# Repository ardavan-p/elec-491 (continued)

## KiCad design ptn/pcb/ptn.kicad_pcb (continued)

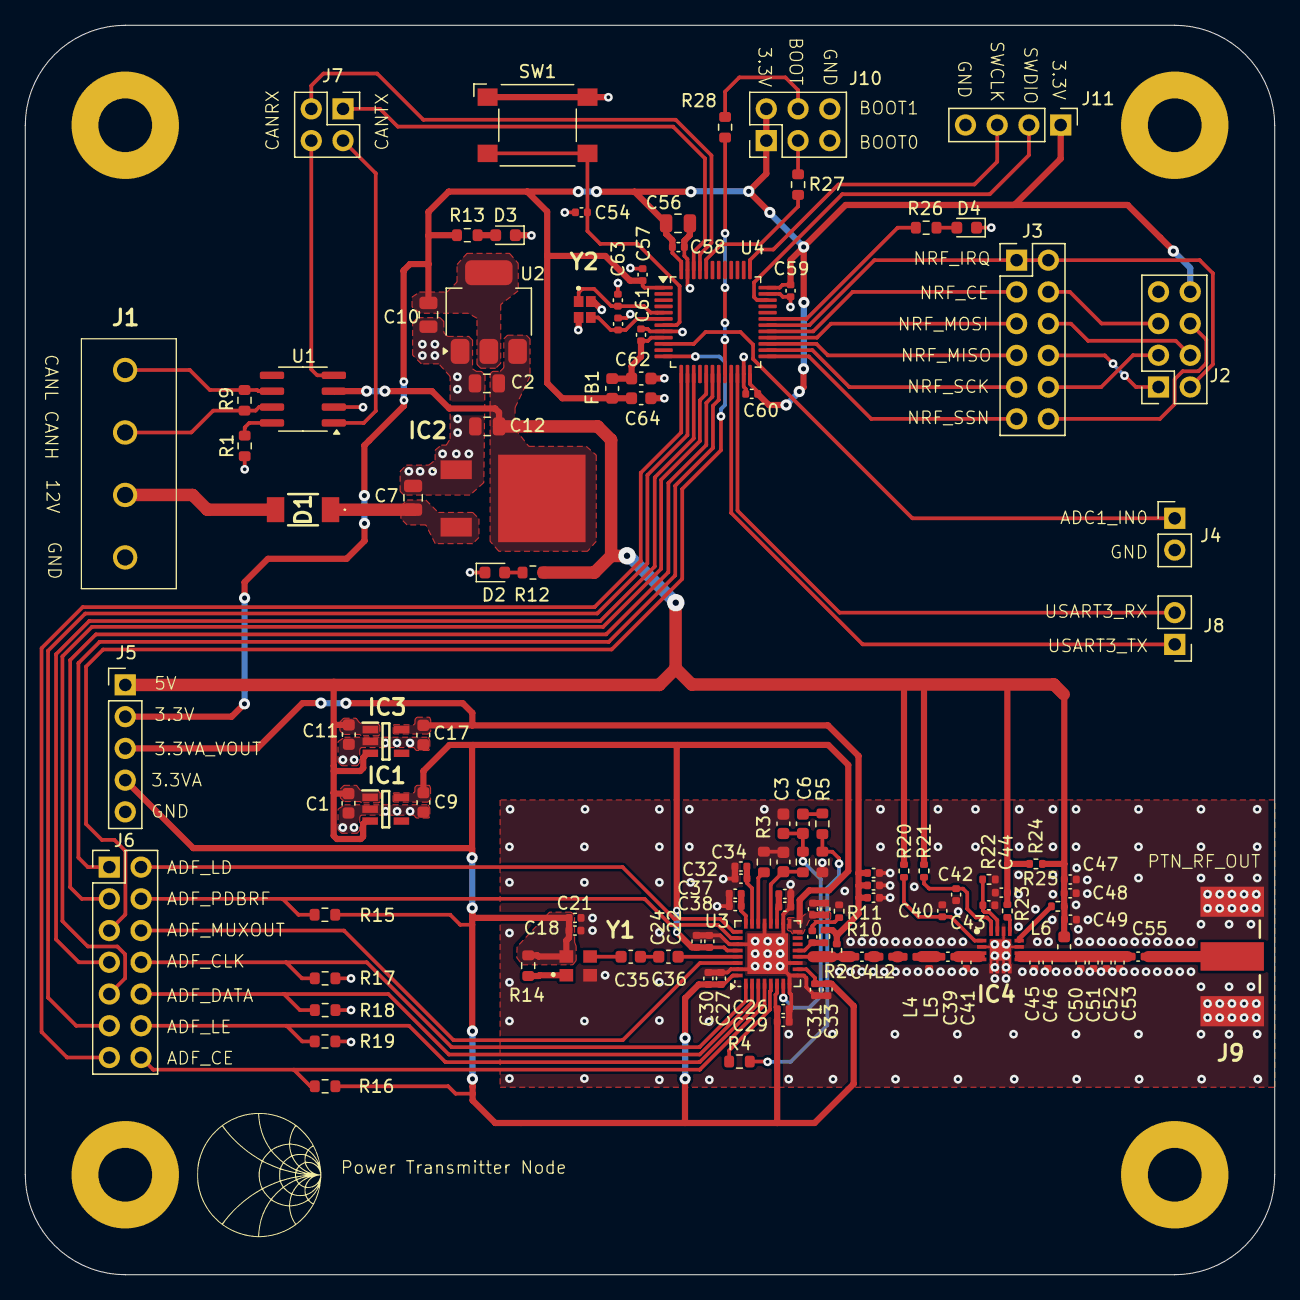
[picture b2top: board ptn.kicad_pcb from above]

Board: 2 copper layers, 100.0 x 100.0 mm, 125 parts (0 on the bottom side), 83 nets.

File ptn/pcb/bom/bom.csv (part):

"Reference","Guerrilla ID","Value","Description","Manufacturer_Name","Manufacturer_Part_Number","Mouser Part Number","Footprint","Qty","Datasheet","DNP"
"J1","","TB002-500-04BE","Fixed Terminal Blocks screw type, 5.00 , horizontal, 4 poles, CUI Blue, slotted screw, PCB mount","CUI Devices","TB002-500-04BE","490-TB002-500-04BE","project_footprint_library:TB00250004BE_SCREW_TERMINAL","1","https://componentsearchengine.com/Datasheets/1/TB002-500-04BE.pdf",""
"SW1","","SW_Push","Push button switch, generic, two pins","Omron Electronics","B3FS-1002P","653-B3FS-1002P","Button_Switch_SMD:SW_SPST_Omron_B3FS-100xP","1","~",""
"U4","","STM32F103C8T6","STMicroelectronics Arm Cortex-M3 MCU, 64KB flash, 20KB RAM, 72 MHz, 2.0-3.6V, 37 GPIO, LQFP48","STMicroelectronics","STM32F103C8T6","511-STM32F103C8T6","Package_QFP:LQFP-48_7x7mm_P0.5mm","1","https://www.st.com/resource/en/datasheet/stm32f103c8.pdf",""
"Y1","","SIT5000AICGE-33E0-25.000000X","TCXO Oscillators 25MHz 3.3V -40C +85C 5ppm","SiTime","SIT5000AICGE-33E0-25.000000X","788-5000AICGE3E0-25X","project_footprint_library:SIT5000AICGE33E025000000X","1","https://componentsearchengine.com/Datasheets/1/SIT5000AICGE-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",""
"U2","","NCP1117-3.3_SOT223","1A Low drop-out regulator, Fixed Output 3.3V, SOT-223","onsemi","NCP1117ST33T3G","863-NCP1117ST33T3G","Package_TO_SOT_SMD:SOT-223-3_TabPin2","1","http://www.onsemi.com/pub_link/Collateral/NCP1117-D.PDF",""
"U1","","MCP2551-I-SN","High-Speed CAN Transceiver, 1Mbps, 5V supply, SOIC-8","Microchip Technology","MCP2551-I/SN","579-MCP2551-I/SN","Package_SO:SOIC-8_3.9x4.9mm_P1.27mm","1","http://ww1.microchip.com/downloads/en/devicedoc/21667d.pdf",""
"D2,D3,D4","","LED","Light emitting diode 150060VS55040","Wurth Elektronik","150060VS55040","710-150060VS55040","LED_SMD:LED_0603_1608Metric","3","~",""
"IC4","","GRF5509","RF Amplifier High Efficiency, 5.0Watt PA/Saturated PA, OP1dB >34.0 dBm, 900 MHz ISM; 0.7 - 01.8 GHz","Guerrilla RF","GRF5509","459-GRF5509","project_footprint_library:QFN50P300X300X85-17N","1","https://www.guerrilla-rf.com/products/DataSheet?sku=5509&fil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",""
"D1","","D","Diode","ROHM Semiconductor","RF302LAM2STR","755-RF302LAM2STR","project_footprint_library:RF302LAM2STR_DIODE","1","~",""
"IC2","","AZ1084CD-5.0TRG1","Linear Voltage Regulator IC Positive Fixed 1 Output 5A TO-252-3","Diodes Incorporated","AZ1084CD-5.0TRG1","621-AZ1084CD-5.0TRG1","project_footprint_library:AZ1084CD50TRG1_LDO_5V","1","https://www.diodes.com//assets/Datasheets/AZ1084C.pdf",""
"IC1,IC3","","ADP150AUJZ-3.3-R7","Ultralow Noise, 150 mA CMOS Linear Regulator","Analog Devices","ADP150AUJZ-3.3-R7","584-ADP150AUJZ-3.3R7","project_footprint_library:SOT95P280X100-5N","2","https://componentsearchengine.com/Datasheets/1/ADP150AUJZ-3.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",""
"U3","","ADF4351","35-4400MHz fractional-N PLL, LFCSP-32","Analog Devices","ADF4351BCPZ-RL7","584-ADF4351BCPZ-R7","Package_CSP:LFCSP-32-1EP_5x5mm_P0.5mm_EP3.25x3.25mm","1","https://www.analog.com/media/en/technical-documentation/data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",""
"J9","","142-0701-801","JOHNSON - 142-0701-801 - \u5C04\u9891/\u540C\u8F74\u63D2\u5B54, SMA, PCB\u5B89\u88C5","Cinch Connectivity Solutions","142-0701-801","530-142-0701-801","project_footprint_library:142-0701-851","1","",""
"Y2","","16MHz","Four pin crystal, GND on pins 2 and 4. Wurth PN: 830108288709","Wurth Elektronik","830108288709","710-830108288709","project_footprint_library:16MHz_830108288709","1","~",""
"R15,R16,R17,R18,R19,R27,R28","","10k","Resistor","YAGEO","RT0603FRE1310KL","603-RT0603FRE1310KL","Resistor_SMD:R_0603_1608Metric","7","~",""
"R21","M3","6.8k","Resistor M3","Panasonic","ERJ-2GEJ682X","667-ERJ-2GEJ682X","Resistor_SMD:R_0402_1005Metric","1","~",""
"R3","","5.1k","Resistor","Vishay / Dale","CRCW06035K10FKEC","71-CRCW06035K10FKEC","Resistor_SMD:R_0603_1608Metric","1","~",""
"R20","M1","3.3k","Resistor M1","Panasonic","ERJ-2GEJ332X","667-ERJ-2GEJ332X","Resistor_SMD:R_0402_1005Metric","1","~",""
"R14","","2k","Resistor","YAGEO","RT0603FRE102KL","603-RT0603FRE102KL","Resistor_SMD:R_0603_1608Metric","1","~",""
"R1,R6","","1k","Resistor","YAGEO","RC0603FR-101KL","603-RC0603FR-101KL","Resistor_SMD:R_0603_1608Metric","2","~",""
"R5","","360R","Resistor","YAGEO","RT0603DRE07360RL","603-RT0603DRE07360RL","Resistor_SMD:R_0603_1608Metric","1","~",""
"R12","","250R","Resistor","YAGEO","RT0603BRE07250RL","603-RT0603BRE07250RL","Resistor_SMD:R_0603_1608Metric","1","~",""
"R9","","120R","Resistor","YAGEO","RC0603FR-10120RL","603-RC0603FR-10120RL","Resistor_SMD:R_0603_1608Metric","1","~",""
"FB1","","120R","Ferrite bead - 120 ohms at 100MHz","Bussmann / Eaton","MFBM1V1608-121-R","704-MFBM1V1608-121-R","Inductor_SMD:L_0603_1608Metric","1","~",""
"R13,R26","","100R","Resistor","YAGEO","RT0603DRE07100RL","603-RT0603DRE07100RL","Resistor_SMD:R_0603_1608Metric","2","~",""
"R2,R10,R11","","50R","Resistor","YAGEO","RC0402JR-0750RL","603-RC0402JR-0750RL","Resistor_SMD:R_0402_1005Metric","3","~",""
"C12","","22u","Unpolarized capacitor","Murata Electronics","GRM21BR61E226ME44K","81-GRM21BR61E226ME4K","Capacitor_SMD:C_0805_2012Metric","1","~",""
"C2,C7,C10,C56","","10u","Unpolarized capacitor","Murata Electronics","GRM21BR61E106KA73K","81-GRM21BR61E106KA3K","Capacitor_SMD:C_0805_2012Metric","4","~",""
"C1,C9,C11,C17,C62,C64","","1u","Unpolarized capacitor","KEMET","C0603C105K3PACTU","80-C0603C105K3P","Capacitor_SMD:C_0603_1608Metric","6","~",""
"C19,C20,C21,C24,C28,C29,C30,C33,C34,C38,C44,C48,C54,C57,C58,C59,C60","-- mixed values --","0.1u","-- mixed values --","Murata Electronics","GRM155R71C104JA88J","81-GRM155R71C104JA8J","Capacitor_SMD:C_0402_1005Metric","17","~",""
"C6","","47n","Unpolarized capacitor","KEMET","C0603C473J3RACTU","80-C0603C473J3R","Capacitor_SMD:C_0603_1608Metric","1","~",""
"L6","M18","24n","Inductor M18","Murata Electronics","LQW18AN24NG80D","81-LQW18AN24NG80D","Inductor_SMD:L_0603_1608Metric","1","~",""
"C61","","10n","Unpolarized capacitor","KEMET","C0402C103J8RACTU","80-C0402C103J8RACTU","Capacitor_SMD:C_0402_1005Metric","1","~",""
"L1,L3","","7.5n","Inductor","Murata Electronics","LQW15AN7N5G80D","81-LQW15AN7N5G80D","Inductor_SMD:L_0402_1005Metric","2","~","DNP"
"L4,L5","-- mixed values --","6.8n","-- mixed values --","Murata Electronics","LQG15WH6N8G02D","81-LQG15WH6N8G02D","Inductor_SMD:L_0402_1005Metric","2","~",""
"C3","","2.7n","Unpolarized capacitor","KYOCERA AVX","06031C272JAT2A","581-06031C272JAT2A","Capacitor_SMD:C_0603_1608Metric","1","~",""
"L2","","1.9n","Inductor","Murata Electronics","LQG15WZ1N9C02D","81-LQG15WZ1N9C02D","Inductor_SMD:L_0402_1005Metric","1","~",""
"C8","","1.2n","Unpolarized capacitor","KEMET","C0603C122J5RACTU","80-C0603C122J5R","Capacitor_SMD:C_0603_1608Metric","1","~",""
"C35,C36","","1n","Unpolarized capacitor","KYOCERA AVX","06035A102JAT2A","581-06035A102J","Capacitor_SMD:C_0603_1608Metric","2","~",""
"C5,C14","","1n","Unpolarized capacitor","Murata Electronics","GRM1555C1H102FA01D","81-GRM1555C1H102FA1D","Capacitor_SMD:C_0402_1005Metric","2","~","DNP"
"C16,C23","","120p","Unpolarized capacitor","Murata Electronics","GRM1555C1H121FA01D","81-GRM1555C1H121FA1D","Capacitor_SMD:C_0402_1005Metric","2","~",""
"C4,C13,C49","-- mixed values --","100p","-- mixed values --","Murata Electronics","GRM1555C1H101FA01D","81-GRM1555C1H101FA1D","Capacitor_SMD:C_0402_1005Metric","3","~",""
"C55","M23","20p","Unpolarized capacitor M23","Murata Electronics","GJM1555C1H200FB01D","81-GJM1555C1H200FB1D","Capacitor_SMD:C_0402_1005Metric","1","~",""
"C53","M22","12p","Unpolarized capacitor M22","Murata Electronics","GJM1555C1H120FB01D","81-GJM1555C1H120FB1D","Capacitor_SMD:C_0402_1005Metric","1","~",""
"C15,C18,C22,C25,C26,C27,C31,C32,C37,C63,C65","","10p","Unpolarized capacitor","Murata Electronics","GCM1555C1H100JA16J","81-GCM1555C1H100JA6J","Capacitor_SMD:C_0402_1005Metric","11","~",""
"C39","M4","5.6p","Unpolarized capacitor M4","Murata Electronics","GJM1555C1H5R6WB01D","81-GJM1555C1H5R6WB1D","Capacitor_SMD:C_0402_1005Metric","1","~",""
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
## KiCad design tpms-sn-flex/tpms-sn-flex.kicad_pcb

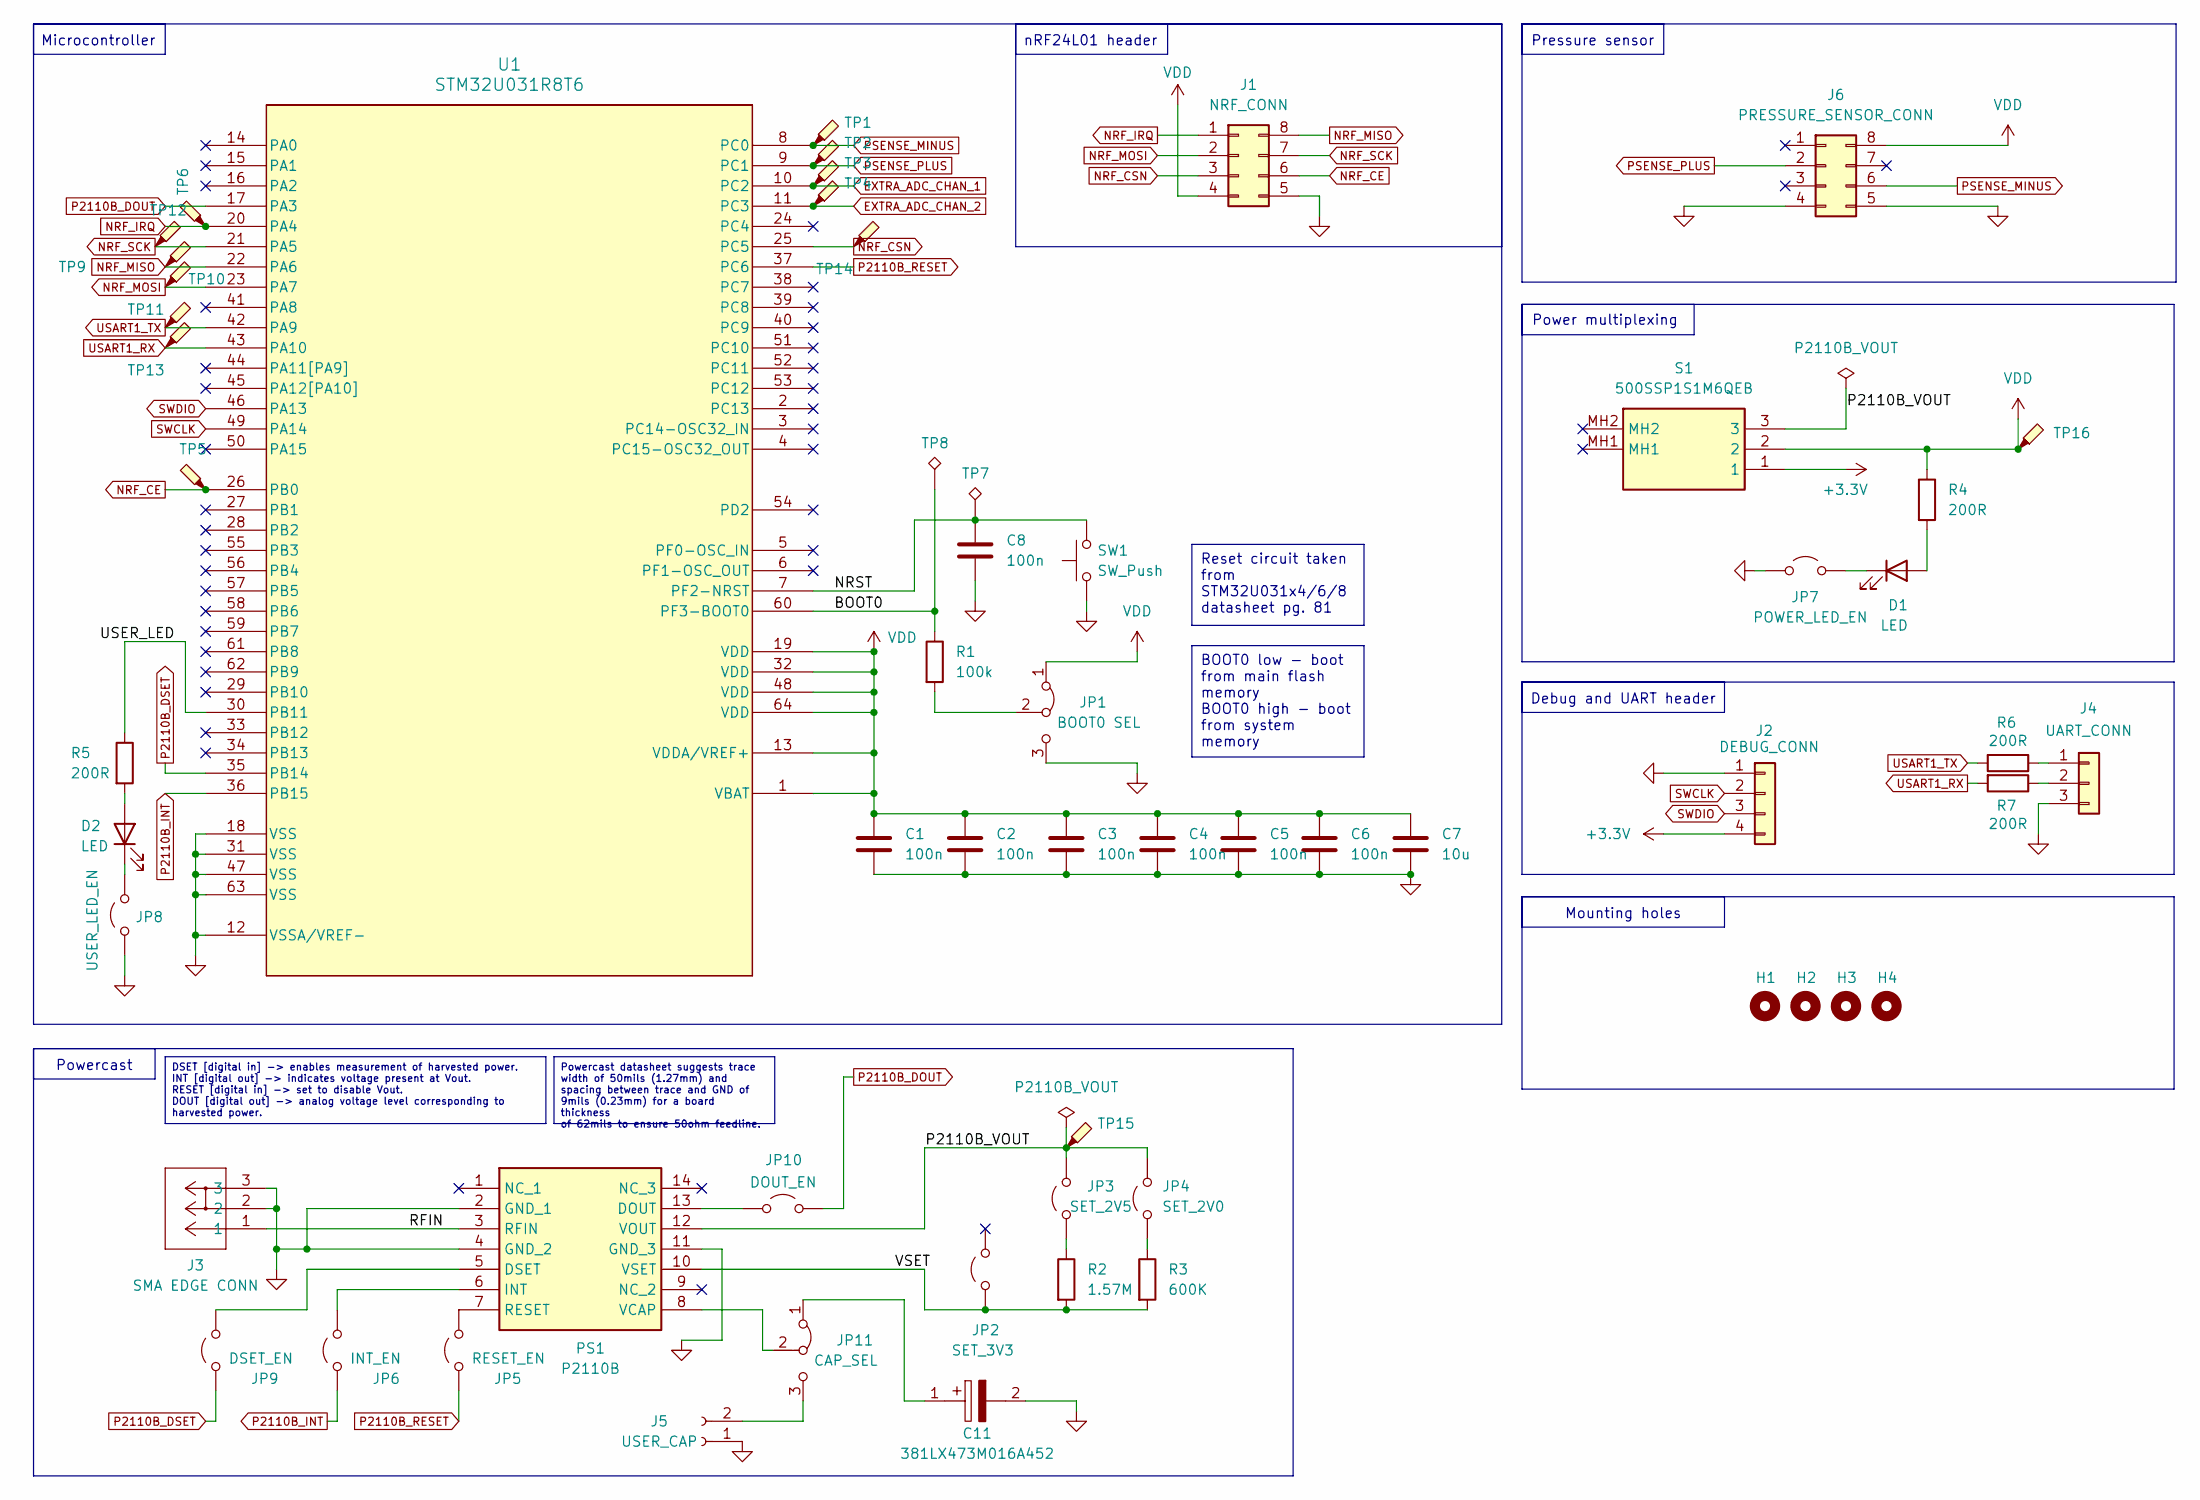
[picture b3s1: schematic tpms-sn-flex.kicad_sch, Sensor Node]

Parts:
C1, C2, C3, C4, C5, C6, C8: 100n; C_0603_1608Metric
C7: 10u; C_0603_1608Metric
C11: 381LX473M016A452; CAPPRD1000W200D3550H4700; Mouser Part Number 598-81LX473M016A452
D1, D2: LED; LED_0603_1608Metric
H1, H2, H3, H4: MountingHole; MountingHole_2.2mm_M2
J1: NRF_CONN; PinSocket_2x04_P2.54mm_Vertical
J2: DEBUG_CONN; PinHeader_1x04_P2.54mm_Vertical
J3: SMA EDGE CONN; CONN_73251-1150_MOL
J4: UART_CONN; PinHeader_1x03_P2.54mm_Vertical
J5: USER_CAP; PinSocket_1x02_P2.54mm_Vertical
J6: PRESSURE_SENSOR_CONN; 8-SOIC-DIP-8-ADAPTER
JP1: BOOT0 SEL; PinHeader_1x03_P2.54mm_Vertical
JP2: SET_3V3; PinHeader_1x02_P2.54mm_Vertical
JP3: SET_2V5; PinHeader_1x02_P2.54mm_Vertical
JP4: SET_2V0; PinHeader_1x02_P2.54mm_Vertical
JP5: RESET_EN; PinHeader_1x02_P2.54mm_Vertical
JP6: INT_EN; PinHeader_1x02_P2.54mm_Vertical
JP7: POWER_LED_EN; PinHeader_1x02_P2.54mm_Vertical
JP8: USER_LED_EN; PinHeader_1x02_P2.54mm_Vertical
JP9: DSET_EN; PinHeader_1x02_P2.54mm_Vertical
JP10: DOUT_EN; PinHeader_1x02_P2.54mm_Vertical
JP11: CAP_SEL; PinHeader_1x03_P2.54mm_Vertical
PS1: P2110B; Mouser Part Number 582-P2110B
R1: 100k; R_0603_1608Metric
R2: 1.57M; R_0603_1608Metric
R3: 600K; R_0603_1608Metric
R4, R5, R6, R7: 200R; R_0603_1608Metric
S1: 500SSP1S1M6QEB; Mouser Part Number 612-500SSP1S1M6QEB
SW1: SW_Push; SW_SPST_Omron_B3FS-100xP
TP1, TP2, TP3, TP4, TP5, TP6: TestPoint_Probe; TestPoint_Pad_2.0x2.0mm
TP7, TP8: TestPoint_Alt; TestPoint_Pad_2.0x2.0mm
TP9, TP10, TP11, TP12, TP13, TP14, TP15, TP16: TestPoint_Pad_2.0x2.0mm
U1: STM32U031R8T6; LQFP64_STM

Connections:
+3.3V: J2.4, S1.1
/BOOT0: R1.1, TP8.1, U1.60 (PF3-BOOT0)
/NRST: C8.1, SW1.2, TP7.1, U1.7 (PF2-NRST)
/P2110B_VOUT: JP3.2 (B), JP4.2 (B), PS1.12 (VOUT), S1.3, TP15.1
/RFIN: J3.1, PS1.3 (RFIN)
/USER_LED: R5.1, U1.30 (PB11)
/VSET: JP2.1 (A), PS1.10 (VSET), R2.2, R3.2
EXTRA_ADC_CHAN_1: TP3.1, U1.10 (PC2)
EXTRA_ADC_CHAN_2: TP4.1, U1.11 (PC3)
GND: C1.2, C2.2, C3.2, C4.2, C5.2, C6.2, C7.2, C8.2, C11.2, H1.1, H2.1, H3.1, H4.1, J1.5, J2.1, J3.2, J3.3, J4.3, J5.1, J6.4, J6.5, JP1.3 (B), JP7.1 (A), JP8.1 (A), PS1.2 (GND_1), PS1.4 (GND_2), PS1.11 (GND_3), SW1.1, U1.12 (VSSA/VREF-), U1.18 (VSS), U1.31 (VSS), U1.47 (VSS), U1.63 (VSS)
NRF_CE: J1.6, TP5.1, U1.26 (PB0)
NRF_CSN: J1.3, TP14.1, U1.25 (PC5)
NRF_IRQ: J1.1, TP6.1, U1.20 (PA4)
NRF_MISO: J1.8, TP9.1, U1.22 (PA6)
NRF_MOSI: J1.2, TP10.1, U1.23 (PA7)
NRF_SCK: J1.7, TP12.1, U1.21 (PA5)
unnamed: D1.2 (A), R4.2
unnamed: D1.1 (K), JP7.2 (B)
unnamed: D2.2 (A), R5.2
unnamed: D2.1 (K), JP8.2 (B)
unnamed: J4.1, R6.1
unnamed: J4.2, R7.1
unnamed: J5.2, JP11.3 (B)
unnamed: JP1.2 (C), R1.2
unnamed: JP3.1 (A), R2.1
unnamed: JP4.1 (A), R3.1
unnamed: JP5.2 (B), PS1.7 (RESET)
unnamed: JP6.2 (B), PS1.6 (INT)
unnamed: JP9.2 (B), PS1.5 (DSET)
unnamed: JP10.1 (A), PS1.13 (DOUT)
unnamed: C11.1, JP11.1 (A)
unnamed: JP11.2 (C), PS1.8 (VCAP)
P2110B_DOUT: JP10.2 (B), U1.17 (PA3)
P2110B_DSET: JP9.1 (A), U1.35 (PB14)
P2110B_INT: JP6.1 (A), U1.36 (PB15)
P2110B_RESET: JP5.1 (A), U1.37 (PC6)
PSENSE_MINUS: J6.6, TP1.1, U1.8 (PC0)
PSENSE_PLUS: J6.2, TP2.1, U1.9 (PC1)
SWCLK: J2.2, U1.49 (PA14)
SWDIO: J2.3, U1.46 (PA13)
USART1_RX: R7.2, TP13.1, U1.43 (PA10)
USART1_TX: R6.2, TP11.1, U1.42 (PA9)
VDD: C1.1, C2.1, C3.1, C4.1, C5.1, C6.1, C7.1, J1.4, J6.8, JP1.1 (A), R4.1, S1.2, TP16.1, U1.1 (VBAT), U1.13 (VDDA/VREF+), U1.19 (VDD), U1.32 (VDD), U1.48 (VDD), U1.64 (VDD)

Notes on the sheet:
Reset circuit taken from STM32U031x4/6/8 datasheet pg. 81
Powercast datasheet suggests trace width of 50mils (1.27mm) and spacing between trace and GND of 9mils (0.23mm) for a board thickness of 62mils to ensure 50ohm feedline.
BOOT0 low - boot from main flash memory BOOT0 high - boot from system memory
DSET [digital in] -> enables measurement of harvested power. INT [digital out] -> indicates voltage present at Vout. RESET [digital in] -> set to disable Vout. DOUT [digital out] -> analog voltage level corresponding to harvested power.
nRF24L01 header
Microcontroller
Powercast
Debug and UART header
Mounting holes
Pressure sensor
Power multiplexing

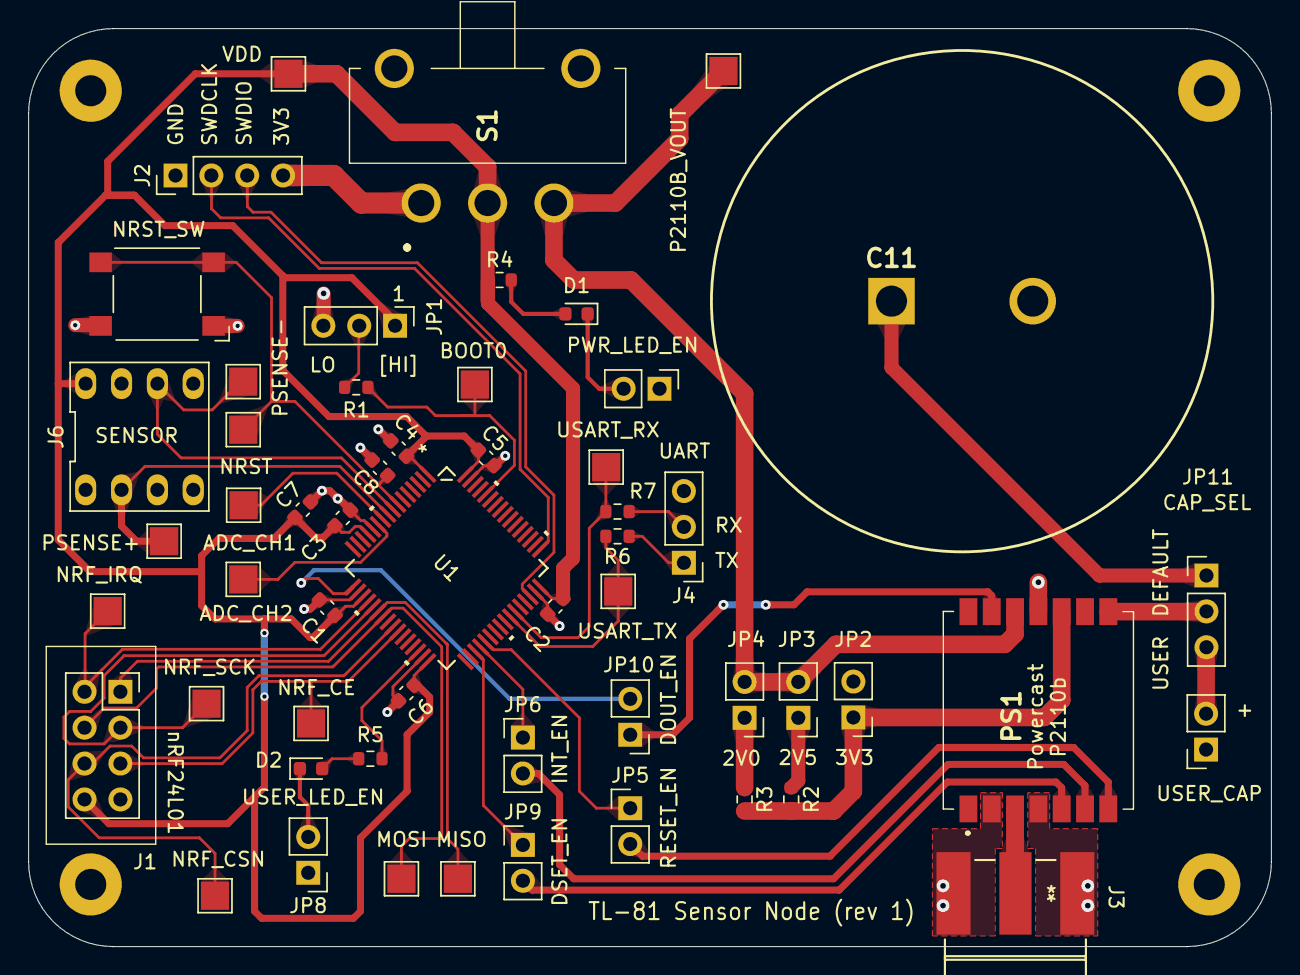
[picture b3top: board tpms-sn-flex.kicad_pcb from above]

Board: 2 copper layers, 88.0 x 65.0 mm, 59 parts (0 on the bottom side), 43 nets.

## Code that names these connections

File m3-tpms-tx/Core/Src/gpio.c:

/* USER CODE BEGIN Header */
/**
  ******************************************************************************
  * @file    gpio.c
  * @brief   This file provides code for the configuration
  *          of all used GPIO pins.
  ******************************************************************************
  * @attention
  *
  * Copyright (c) 2024 STMicroelectronics.
  * All rights reserved.
  *
  * This software is licensed under terms that can be found in the LICENSE file
  * in the root directory of this software component.
  * If no LICENSE file comes with this software, it is provided AS-IS.
  *
  ******************************************************************************
  */
/* USER CODE END Header */

/* Includes ------------------------------------------------------------------*/
#include "gpio.h"

/* USER CODE BEGIN 0 */

/* USER CODE END 0 */

/*----------------------------------------------------------------------------*/
/* Configure GPIO                                                             */
/*----------------------------------------------------------------------------*/
/* USER CODE BEGIN 1 */

/* USER CODE END 1 */

/** Configure pins
     PC14-OSC32_IN   ------> RCC_OSC32_IN
     PC15-OSC32_OUT   ------> RCC_OSC32_OUT
     PF0-OSC_IN   ------> RCC_OSC_IN
     PF1-OSC_OUT   ------> RCC_OSC_OUT
     PA13 (SWDIO)   ------> DEBUG_JTMS-SWDIO
     PA14 (SWCLK)   ------> DEBUG_JTCK-SWCLK
*/
void MX_GPIO_Init(void)
{

  GPIO_InitTypeDef GPIO_InitStruct = {0};

  /* GPIO Ports Clock Enable */
  __HAL_RCC_GPIOC_CLK_ENABLE();
  __HAL_RCC_GPIOF_CLK_ENABLE();
  __HAL_RCC_GPIOA_CLK_ENABLE();
  __HAL_RCC_GPIOB_CLK_ENABLE();
  __HAL_RCC_GPIOD_CLK_ENABLE();

  /*Configure GPIO pin Output Level */
  HAL_GPIO_WritePin(USER_LED_GPIO_Port, USER_LED_Pin, GPIO_PIN_RESET);

  /*Configure GPIO pin Output Level */
  HAL_GPIO_WritePin(GPIOC, P2110B_RESET_Pin|CHIP_SELECT_Pin|CHIP_ENABLE_Pin, GPIO_PIN_RESET);

  /*Configure GPIO pins : PC13 PC0 PC1 PC2
                           PC4 PC5 PC6 PC7
                           PC8 */
  GPIO_InitStruct.Pin = GPIO_PIN_13|GPIO_PIN_0|GPIO_PIN_1|GPIO_PIN_2
                          |GPIO_PIN_4|GPIO_PIN_5|GPIO_PIN_6|GPIO_PIN_7
                          |GPIO_PIN_8;
  GPIO_InitStruct.Mode = GPIO_MODE_ANALOG;
  GPIO_InitStruct.Pull = GPIO_NOPULL;
  HAL_GPIO_Init(GPIOC, &GPIO_InitStruct);

  /*Configure GPIO pins : PF2 PF3 */
  GPIO_InitStruct.Pin = GPIO_PIN_2|GPIO_PIN_3;
  GPIO_InitStruct.Mode = GPIO_MODE_ANALOG;
  GPIO_InitStruct.Pull = GPIO_NOPULL;
  HAL_GPIO_Init(GPIOF, &GPIO_InitStruct);

  /*Configure GPIO pins : PA0 PA2 PA3 PA4
                           PA8 PA9 PA10 PA11
                           PA12 PA15 */
  GPIO_InitStruct.Pin = GPIO_PIN_0|GPIO_PIN_2|GPIO_PIN_3|GPIO_PIN_4
                          |GPIO_PIN_8|GPIO_PIN_9|GPIO_PIN_10|GPIO_PIN_11
                          |GPIO_PIN_12|GPIO_PIN_15;
  GPIO_InitStruct.Mode = GPIO_MODE_ANALOG;
  GPIO_InitStruct.Pull = GPIO_NOPULL;
  HAL_GPIO_Init(GPIOA, &GPIO_InitStruct);

  /*Configure GPIO pin : PtPin */
  GPIO_InitStruct.Pin = USER_LED_Pin;
  GPIO_InitStruct.Mode = GPIO_MODE_OUTPUT_PP;
  GPIO_InitStruct.Pull = GPIO_NOPULL;
  GPIO_InitStruct.Speed = GPIO_SPEED_FREQ_LOW;
  HAL_GPIO_Init(USER_LED_GPIO_Port, &GPIO_InitStruct);

  /*Configure GPIO pins : PB0 PB1 PB2 PB10
                           PB11 PB12 PB13 PB14
                           PB15 PB3 PB4 PB5
                           PB6 PB7 PB8 PB9 */
  GPIO_InitStruct.Pin = GPIO_PIN_0|GPIO_PIN_1|GPIO_PIN_2|GPIO_PIN_10
                          |GPIO_PIN_11|GPIO_PIN_12|GPIO_PIN_13|GPIO_PIN_14
                          |GPIO_PIN_15|GPIO_PIN_3|GPIO_PIN_4|GPIO_PIN_5
                          |GPIO_PIN_6|GPIO_PIN_7|GPIO_PIN_8|GPIO_PIN_9;
  GPIO_InitStruct.Mode = GPIO_MODE_ANALOG;
  GPIO_InitStruct.Pull = GPIO_NOPULL;
  HAL_GPIO_Init(GPIOB, &GPIO_InitStruct);

  /*Configure GPIO pins : PCPin PCPin PCPin */
  GPIO_InitStruct.Pin = P2110B_RESET_Pin|CHIP_SELECT_Pin|CHIP_ENABLE_Pin;
  GPIO_InitStruct.Mode = GPIO_MODE_OUTPUT_PP;
  GPIO_InitStruct.Pull = GPIO_NOPULL;
  GPIO_InitStruct.Speed = GPIO_SPEED_FREQ_LOW;
  HAL_GPIO_Init(GPIOC, &GPIO_InitStruct);

  /*Configure GPIO pin : PtPin */
  GPIO_InitStruct.Pin = N_IRQ_Pin;
  GPIO_InitStruct.Mode = GPIO_MODE_IT_FALLING;
  GPIO_InitStruct.Pull = GPIO_NOPULL;
  HAL_GPIO_Init(N_IRQ_GPIO_Port, &GPIO_InitStruct);

  /*Configure GPIO pin : PD2 */
  GPIO_InitStruct.Pin = GPIO_PIN_2;
  GPIO_InitStruct.Mode = GPIO_MODE_ANALOG;
  GPIO_InitStruct.Pull = GPIO_NOPULL;
  HAL_GPIO_Init(GPIOD, &GPIO_InitStruct);

  /* EXTI interrupt init*/
  HAL_NVIC_SetPriority(EXTI4_15_IRQn, 0, 0);
  HAL_NVIC_EnableIRQ(EXTI4_15_IRQn);

}

/* USER CODE BEGIN 2 */

/* USER CODE END 2 */

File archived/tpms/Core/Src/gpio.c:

/* USER CODE BEGIN Header */
/**
  ******************************************************************************
  * @file    gpio.c
  * @brief   This file provides code for the configuration
  *          of all used GPIO pins.
  ******************************************************************************
  * @attention
  *
  * Copyright (c) 2024 STMicroelectronics.
  * All rights reserved.
  *
  * This software is licensed under terms that can be found in the LICENSE file
  * in the root directory of this software component.
  * If no LICENSE file comes with this software, it is provided AS-IS.
  *
  ******************************************************************************
  */
/* USER CODE END Header */

/* Includes ------------------------------------------------------------------*/
#include "gpio.h"

/* USER CODE BEGIN 0 */

/* USER CODE END 0 */

/*----------------------------------------------------------------------------*/
/* Configure GPIO                                                             */
/*----------------------------------------------------------------------------*/
/* USER CODE BEGIN 1 */

/* USER CODE END 1 */

/** Configure pins
     PC14-OSC32_IN   ------> RCC_OSC32_IN
     PC15-OSC32_OUT   ------> RCC_OSC32_OUT
     PF0-OSC_IN   ------> RCC_OSC_IN
     PF1-OSC_OUT   ------> RCC_OSC_OUT
     PA13 (SWDIO)   ------> DEBUG_JTMS-SWDIO
     PA14 (SWCLK)   ------> DEBUG_JTCK-SWCLK
     PB8   ------> I2C1_SCL
     PB9   ------> I2C1_SDA
*/
void MX_GPIO_Init(void)
{

  GPIO_InitTypeDef GPIO_InitStruct = {0};

  /* GPIO Ports Clock Enable */
  __HAL_RCC_GPIOC_CLK_ENABLE();
  __HAL_RCC_GPIOF_CLK_ENABLE();
  __HAL_RCC_GPIOA_CLK_ENABLE();
  __HAL_RCC_GPIOB_CLK_ENABLE();
  __HAL_RCC_GPIOD_CLK_ENABLE();

  /*Configure GPIO pin Output Level */
  HAL_GPIO_WritePin(USER_LED_GPIO_Port, USER_LED_Pin, GPIO_PIN_RESET);

  /*Configure GPIO pin Output Level */
  HAL_GPIO_WritePin(GPIOC, CHIP_SELECT_Pin|CHIP_ENABLE_Pin, GPIO_PIN_RESET);

  /*Configure GPIO pins : PC13 PC0 PC1 PC2
                           PC3 PC4 PC5 PC6
                           PC7 PC8 PC9 */
  GPIO_InitStruct.Pin = GPIO_PIN_13|GPIO_PIN_0|GPIO_PIN_1|GPIO_PIN_2
                          |GPIO_PIN_3|GPIO_PIN_4|GPIO_PIN_5|GPIO_PIN_6
                          |GPIO_PIN_7|GPIO_PIN_8|GPIO_PIN_9;
  GPIO_InitStruct.Mode = GPIO_MODE_ANALOG;
  GPIO_InitStruct.Pull = GPIO_NOPULL;
  HAL_GPIO_Init(GPIOC, &GPIO_InitStruct);

  /*Configure GPIO pins : PF2 PF3 */
  GPIO_InitStruct.Pin = GPIO_PIN_2|GPIO_PIN_3;
  GPIO_InitStruct.Mode = GPIO_MODE_ANALOG;
  GPIO_InitStruct.Pull = GPIO_NOPULL;
  HAL_GPIO_Init(GPIOF, &GPIO_InitStruct);

  /*Configure GPIO pins : PA0 PA4 PA8 PA9
                           PA10 PA11 PA12 PA15 */
  GPIO_InitStruct.Pin = GPIO_PIN_0|GPIO_PIN_4|GPIO_PIN_8|GPIO_PIN_9
                          |GPIO_PIN_10|GPIO_PIN_11|GPIO_PIN_12|GPIO_PIN_15;
  GPIO_InitStruct.Mode = GPIO_MODE_ANALOG;
  GPIO_InitStruct.Pull = GPIO_NOPULL;
  HAL_GPIO_Init(GPIOA, &GPIO_InitStruct);

  /*Configure GPIO pin : PtPin */
  GPIO_InitStruct.Pin = USER_LED_Pin;
  GPIO_InitStruct.Mode = GPIO_MODE_OUTPUT_PP;
  GPIO_InitStruct.Pull = GPIO_NOPULL;
  GPIO_InitStruct.Speed = GPIO_SPEED_FREQ_LOW;
  HAL_GPIO_Init(USER_LED_GPIO_Port, &GPIO_InitStruct);

  /*Configure GPIO pins : PB0 PB1 PB2 PB10
                           PB11 PB12 PB13 PB14
                           PB15 PB3 PB4 PB5
                           PB6 PB7 */
  GPIO_InitStruct.Pin = GPIO_PIN_0|GPIO_PIN_1|GPIO_PIN_2|GPIO_PIN_10
                          |GPIO_PIN_11|GPIO_PIN_12|GPIO_PIN_13|GPIO_PIN_14
                          |GPIO_PIN_15|GPIO_PIN_3|GPIO_PIN_4|GPIO_PIN_5
                          |GPIO_PIN_6|GPIO_PIN_7;
  GPIO_InitStruct.Mode = GPIO_MODE_ANALOG;
  GPIO_InitStruct.Pull = GPIO_NOPULL;
  HAL_GPIO_Init(GPIOB, &GPIO_InitStruct);

  /*Configure GPIO pins : PCPin PCPin */
  GPIO_InitStruct.Pin = CHIP_SELECT_Pin|CHIP_ENABLE_Pin;
  GPIO_InitStruct.Mode = GPIO_MODE_OUTPUT_PP;
  GPIO_InitStruct.Pull = GPIO_NOPULL;
  GPIO_InitStruct.Speed = GPIO_SPEED_FREQ_LOW;
  HAL_GPIO_Init(GPIOC, &GPIO_InitStruct);

  /*Configure GPIO pin : PtPin */
  GPIO_InitStruct.Pin = NRF_IRQ_Pin;
  GPIO_InitStruct.Mode = GPIO_MODE_IT_FALLING;
  GPIO_InitStruct.Pull = GPIO_NOPULL;
  HAL_GPIO_Init(NRF_IRQ_GPIO_Port, &GPIO_InitStruct);

  /*Configure GPIO pin : PD2 */
  GPIO_InitStruct.Pin = GPIO_PIN_2;
  GPIO_InitStruct.Mode = GPIO_MODE_ANALOG;
  GPIO_InitStruct.Pull = GPIO_NOPULL;
  HAL_GPIO_Init(GPIOD, &GPIO_InitStruct);

  /*Configure GPIO pins : PBPin PBPin */
  GPIO_InitStruct.Pin = I2C1_SCL_Pin|I2C1_SDA_Pin;
  GPIO_InitStruct.Mode = GPIO_MODE_AF_OD;
  GPIO_InitStruct.Pull = GPIO_NOPULL;
  GPIO_InitStruct.Speed = GPIO_SPEED_FREQ_LOW;
  GPIO_InitStruct.Alternate = GPIO_AF4_I2C1;
  HAL_GPIO_Init(GPIOB, &GPIO_InitStruct);

  /* EXTI interrupt init*/
  HAL_NVIC_SetPriority(EXTI4_15_IRQn, 0, 0);
  HAL_NVIC_EnableIRQ(EXTI4_15_IRQn);

}

/* USER CODE BEGIN 2 */

/* USER CODE END 2 */

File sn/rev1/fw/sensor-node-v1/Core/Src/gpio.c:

/* USER CODE BEGIN Header */
/**
  ******************************************************************************
  * @file    gpio.c
  * @brief   This file provides code for the configuration
  *          of all used GPIO pins.
  ******************************************************************************
  * @attention
  *
  * Copyright (c) 2024 STMicroelectronics.
  * All rights reserved.
  *
  * This software is licensed under terms that can be found in the LICENSE file
  * in the root directory of this software component.
  * If no LICENSE file comes with this software, it is provided AS-IS.
  *
  ******************************************************************************
  */
/* USER CODE END Header */

/* Includes ------------------------------------------------------------------*/
#include "gpio.h"

/* USER CODE BEGIN 0 */

/* USER CODE END 0 */

/*----------------------------------------------------------------------------*/
/* Configure GPIO                                                             */
/*----------------------------------------------------------------------------*/
/* USER CODE BEGIN 1 */

/* USER CODE END 1 */

/** Configure pins
     PA13 (SWDIO)   ------> DEBUG_JTMS-SWDIO
     PA14 (SWCLK)   ------> DEBUG_JTCK-SWCLK
*/
void MX_GPIO_Init(void)
{

  GPIO_InitTypeDef GPIO_InitStruct = {0};

  /* GPIO Ports Clock Enable */
  __HAL_RCC_GPIOC_CLK_ENABLE();
  __HAL_RCC_GPIOF_CLK_ENABLE();
  __HAL_RCC_GPIOA_CLK_ENABLE();
  __HAL_RCC_GPIOB_CLK_ENABLE();
  __HAL_RCC_GPIOD_CLK_ENABLE();

  /*Configure GPIO pin Output Level */
  HAL_GPIO_WritePin(GPIOC, NRF_CSN_Pin|P2110B_RESET_Pin, GPIO_PIN_RESET);

  /*Configure GPIO pin Output Level */
  HAL_GPIO_WritePin(GPIOB, NRF_CE_Pin|USER_LED_Pin, GPIO_PIN_RESET);

  /*Configure GPIO pins : PC13 PC14 PC15 PC2
                           PC3 PC4 PC7 PC8
                           PC9 PC10 PC11 PC12 */
  GPIO_InitStruct.Pin = GPIO_PIN_13|GPIO_PIN_14|GPIO_PIN_15|GPIO_PIN_2
                          |GPIO_PIN_3|GPIO_PIN_4|GPIO_PIN_7|GPIO_PIN_8
                          |GPIO_PIN_9|GPIO_PIN_10|GPIO_PIN_11|GPIO_PIN_12;
  GPIO_InitStruct.Mode = GPIO_MODE_ANALOG;
  GPIO_InitStruct.Pull = GPIO_NOPULL;
  HAL_GPIO_Init(GPIOC, &GPIO_InitStruct);

  /*Configure GPIO pins : PF0 PF1 PF2 PF3 */
  GPIO_InitStruct.Pin = GPIO_PIN_0|GPIO_PIN_1|GPIO_PIN_2|GPIO_PIN_3;
  GPIO_InitStruct.Mode = GPIO_MODE_ANALOG;
  GPIO_InitStruct.Pull = GPIO_NOPULL;
  HAL_GPIO_Init(GPIOF, &GPIO_InitStruct);

  /*Configure GPIO pins : PA0 PA1 PA2 PA3
                           PA8 PA9 PA10 PA11
                           PA12 PA15 */
  GPIO_InitStruct.Pin = GPIO_PIN_0|GPIO_PIN_1|GPIO_PIN_2|GPIO_PIN_3
                          |GPIO_PIN_8|GPIO_PIN_9|GPIO_PIN_10|GPIO_PIN_11
                          |GPIO_PIN_12|GPIO_PIN_15;
  GPIO_InitStruct.Mode = GPIO_MODE_ANALOG;
  GPIO_InitStruct.Pull = GPIO_NOPULL;
  HAL_GPIO_Init(GPIOA, &GPIO_InitStruct);

  /*Configure GPIO pin : PtPin */
  GPIO_InitStruct.Pin = NRF_IRQ_Pin;
  GPIO_InitStruct.Mode = GPIO_MODE_IT_RISING;
  GPIO_InitStruct.Pull = GPIO_NOPULL;
  HAL_GPIO_Init(NRF_IRQ_GPIO_Port, &GPIO_InitStruct);

  /*Configure GPIO pins : PCPin PCPin */
  GPIO_InitStruct.Pin = NRF_CSN_Pin|P2110B_RESET_Pin;
  GPIO_InitStruct.Mode = GPIO_MODE_OUTPUT_PP;
  GPIO_InitStruct.Pull = GPIO_NOPULL;
  GPIO_InitStruct.Speed = GPIO_SPEED_FREQ_LOW;
  HAL_GPIO_Init(GPIOC, &GPIO_InitStruct);

  /*Configure GPIO pins : PBPin PBPin */
  GPIO_InitStruct.Pin = NRF_CE_Pin|USER_LED_Pin;
  GPIO_InitStruct.Mode = GPIO_MODE_OUTPUT_PP;
  GPIO_InitStruct.Pull = GPIO_NOPULL;
  GPIO_InitStruct.Speed = GPIO_SPEED_FREQ_LOW;
  HAL_GPIO_Init(GPIOB, &GPIO_InitStruct);

  /*Configure GPIO pins : PB1 PB2 PB10 PB12
                           PB13 PB14 PB15 PB3
                           PB4 PB5 PB6 PB7
                           PB8 PB9 */
  GPIO_InitStruct.Pin = GPIO_PIN_1|GPIO_PIN_2|GPIO_PIN_10|GPIO_PIN_12
                          |GPIO_PIN_13|GPIO_PIN_14|GPIO_PIN_15|GPIO_PIN_3
                          |GPIO_PIN_4|GPIO_PIN_5|GPIO_PIN_6|GPIO_PIN_7
                          |GPIO_PIN_8|GPIO_PIN_9;
  GPIO_InitStruct.Mode = GPIO_MODE_ANALOG;
  GPIO_InitStruct.Pull = GPIO_NOPULL;
  HAL_GPIO_Init(GPIOB, &GPIO_InitStruct);

  /*Configure GPIO pin : PD2 */
  GPIO_InitStruct.Pin = GPIO_PIN_2;
  GPIO_InitStruct.Mode = GPIO_MODE_ANALOG;
  GPIO_InitStruct.Pull = GPIO_NOPULL;
  HAL_GPIO_Init(GPIOD, &GPIO_InitStruct);

}

/* USER CODE BEGIN 2 */

/* USER CODE END 2 */

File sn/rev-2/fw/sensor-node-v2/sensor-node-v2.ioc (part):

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Mcu.Name=STM32U031K8Ux
Mcu.Package=UFQFPN32
Mcu.UserName=STM32U031K8Ux
PA0-CK_IN.GPIOParameters=GPIO_Label
PA0-CK_IN.GPIO_Label=PSENSE_OUT
PA0-CK_IN.Mode=IN4
PA0-CK_IN.Signal=ADC1_IN4
PA1.GPIOParameters=GPIO_Label
PA1.GPIO_Label=PSENSE_VREF
PA1.Mode=IN5
PA1.Signal=ADC1_IN5
PA10.GPIOParameters=GPIO_Label
PA10.GPIO_Label=P2110B_INT
PA10.Signal=GPIO_Input
PA11\ [PA9].GPIOParameters=GPIO_Label
PA11\ [PA9].GPIO_Label=P2110B_RESET
PA11\ [PA9].Signal=GPIO_Output
PA13\ (SWDIO).Mode=Serial_Wire
PA13\ (SWDIO).Signal=DEBUG_JTMS-SWDIO
PA14\ (SWCLK).Mode=Serial_Wire
PA14\ (SWCLK).Signal=DEBUG_JTCK-SWCLK
PA15.GPIOParameters=GPIO_Label
PA15.GPIO_Label=NRF_IRQ
PA15.Signal=GPXTI15
PA3.GPIOParameters=GPIO_Label
PA3.GPIO_Label=PSENSE_MINUS
PA3.Mode=IN7
PA3.Signal=ADC1_IN7
PA4.GPIOParameters=GPIO_Label
PA4.GPIO_Label=PSENSE_PLUS
PA4.Mode=IN8
PA4.Signal=ADC1_IN8
PA5.Mode=Asynchronous
PA5.Signal=USART3_TX
PA6.GPIOParameters=GPIO_Label
PA6.GPIO_Label=P2110B_DOUT
PA6.Mode=IN10
PA6.Signal=ADC1_IN10
PA7.Mode=Asynchronous
PA7.Signal=USART3_RX
PA9.GPIOParameters=GPIO_Label
PA9.GPIO_Label=P2110B_DSET
PA9.Signal=GPIO_Output
PB3.GPIOParameters=GPIO_Label
PB3.GPIO_Label=NRF_SCK
PB3.Mode=Full_Duplex_Master
PB3.Signal=SPI1_SCK
PB4.GPIOParameters=GPIO_Label
PB4.GPIO_Label=NRF_MISO
PB4.Mode=Full_Duplex_Master
PB4.Signal=SPI1_MISO
PB5.GPIOParameters=GPIO_Label
PB5.GPIO_Label=NRF_MOSI
PB5.Mode=Full_Duplex_Master
PB5.Signal=SPI1_MOSI
PB6.GPIOParameters=GPIO_Label
PB6.GPIO_Label=NRF_CSN
PB6.Signal=GPIO_Output
PB7.GPIOParameters=GPIO_Label
PB7.GPIO_Label=NRF_CE
PB7.Signal=GPIO_Output
PC15-OSC32_OUT.GPIOParameters=GPIO_Label
PC15-OSC32_OUT.GPIO_Label=USER_LED
PC15-OSC32_OUT.Signal=GPIO_Output
RCC.HSE_VALUE=4000000
RCC.SYSCLKFreq_VALUE=16000000
RCC.SYSCLKSource=RCC_SYSCLKSOURCE_MSI
board=custom

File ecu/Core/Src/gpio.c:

/* USER CODE BEGIN Header */
/**
  ******************************************************************************
  * @file    gpio.c
  * @brief   This file provides code for the configuration
  *          of all used GPIO pins.
  ******************************************************************************
  * @attention
  *
  * Copyright (c) 2024 STMicroelectronics.
  * All rights reserved.
  *
  * This software is licensed under terms that can be found in the LICENSE file
  * in the root directory of this software component.
  * If no LICENSE file comes with this software, it is provided AS-IS.
  *
  ******************************************************************************
  */
/* USER CODE END Header */

/* Includes ------------------------------------------------------------------*/
#include "gpio.h"

/* USER CODE BEGIN 0 */

/* USER CODE END 0 */

/*----------------------------------------------------------------------------*/
/* Configure GPIO                                                             */
/*----------------------------------------------------------------------------*/
/* USER CODE BEGIN 1 */

/* USER CODE END 1 */

/** Configure pins as
        * Analog
        * Input
        * Output
        * EVENT_OUT
        * EXTI
        * Free pins are configured automatically as Analog (this feature is enabled through
        * the Code Generation settings)
*/
void MX_GPIO_Init(void)
{

  GPIO_InitTypeDef GPIO_InitStruct = {0};

  /* GPIO Ports Clock Enable */
  __HAL_RCC_GPIOC_CLK_ENABLE();
  __HAL_RCC_GPIOD_CLK_ENABLE();
  __HAL_RCC_GPIOA_CLK_ENABLE();
  __HAL_RCC_GPIOB_CLK_ENABLE();

  /*Configure GPIO pin Output Level */
  HAL_GPIO_WritePin(USER_GPIO_GPIO_Port, USER_GPIO_Pin, GPIO_PIN_RESET);

  /*Configure GPIO pins : PC13 PC0 PC1 PC2
                           PC3 PC4 PC5 PC6
                           PC7 PC8 PC9 PC10
                           PC11 PC12 */
  GPIO_InitStruct.Pin = GPIO_PIN_13|GPIO_PIN_0|GPIO_PIN_1|GPIO_PIN_2
                          |GPIO_PIN_3|GPIO_PIN_4|GPIO_PIN_5|GPIO_PIN_6
                          |GPIO_PIN_7|GPIO_PIN_8|GPIO_PIN_9|GPIO_PIN_10
                          |GPIO_PIN_11|GPIO_PIN_12;
  GPIO_InitStruct.Mode = GPIO_MODE_ANALOG;
  HAL_GPIO_Init(GPIOC, &GPIO_InitStruct);

  /*Configure GPIO pins : PD0 PD1 PD2 */
  GPIO_InitStruct.Pin = GPIO_PIN_0|GPIO_PIN_1|GPIO_PIN_2;
  GPIO_InitStruct.Mode = GPIO_MODE_ANALOG;
  HAL_GPIO_Init(GPIOD, &GPIO_InitStruct);

  /*Configure GPIO pins : PA0 PA1 PA2 PA3
                           PA4 PA5 PA6 PA7
                           PA11 PA12 PA15 */
  GPIO_InitStruct.Pin = GPIO_PIN_0|GPIO_PIN_1|GPIO_PIN_2|GPIO_PIN_3
                          |GPIO_PIN_4|GPIO_PIN_5|GPIO_PIN_6|GPIO_PIN_7
                          |GPIO_PIN_11|GPIO_PIN_12|GPIO_PIN_15;
  GPIO_InitStruct.Mode = GPIO_MODE_ANALOG;
  HAL_GPIO_Init(GPIOA, &GPIO_InitStruct);

  /*Configure GPIO pins : PB0 PB1 PB2 PB10
                           PB11 PB12 PB13 PB14
                           PB15 PB3 PB4 PB5
                           PB6 PB7 */
  GPIO_InitStruct.Pin = GPIO_PIN_0|GPIO_PIN_1|GPIO_PIN_2|GPIO_PIN_10
                          |GPIO_PIN_11|GPIO_PIN_12|GPIO_PIN_13|GPIO_PIN_14
                          |GPIO_PIN_15|GPIO_PIN_3|GPIO_PIN_4|GPIO_PIN_5
                          |GPIO_PIN_6|GPIO_PIN_7;
  GPIO_InitStruct.Mode = GPIO_MODE_ANALOG;
  HAL_GPIO_Init(GPIOB, &GPIO_InitStruct);

  /*Configure GPIO pin : PtPin */
  GPIO_InitStruct.Pin = USER_GPIO_Pin;
  GPIO_InitStruct.Mode = GPIO_MODE_OUTPUT_PP;
  GPIO_InitStruct.Pull = GPIO_NOPULL;
  GPIO_InitStruct.Speed = GPIO_SPEED_FREQ_LOW;
  HAL_GPIO_Init(USER_GPIO_GPIO_Port, &GPIO_InitStruct);

  /*Configure peripheral I/O remapping */
  __HAL_AFIO_REMAP_PD01_ENABLE();

}

/* USER CODE BEGIN 2 */

/* USER CODE END 2 */

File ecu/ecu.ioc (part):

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Mcu.Name=STM32F103R(C-D-E)Tx
Mcu.Package=LQFP64
Mcu.UserName=STM32F103RCTx
PA10.Mode=Asynchronous
PA10.Signal=USART1_RX
PA13.Mode=Serial_Wire
PA13.Signal=SYS_JTMS-SWDIO
PA14.Mode=Serial_Wire
PA14.Signal=SYS_JTCK-SWCLK
PA8.GPIOParameters=GPIO_Label
PA8.GPIO_Label=USER_GPIO
PA8.Signal=GPIO_Output
PA9.Mode=Asynchronous
PA9.Signal=USART1_TX
PB8.Mode=CAN_Activate
PB8.Signal=CAN_RX
PB9.Mode=CAN_Activate
PB9.Signal=CAN_TX
PC14-OSC32_IN.Mode=LSE-External-Oscillator
PC14-OSC32_IN.Signal=RCC_OSC32_IN
PC15-OSC32_OUT.Mode=LSE-External-Oscillator
PC15-OSC32_OUT.Signal=RCC_OSC32_OUT
board=custom

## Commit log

2024-03-13 Start access point simulation notebook
2024-03-15 Add 915 MHz simulations, fix bug with 2.4 GHz
2024-03-31 Make basic link budget for TPMS option.
2024-04-02 Improved tpms link budget
2024-05-07 Add antenna validation simulation that works
2024-05-08 Initial commit of TPMS Rx code
2024-05-08 Initial commit of TPMS Tx code
2024-05-08 Add README.md
2024-06-04 Add initial sensor node KiCAD schematic
2024-06-06 Add layout and routing for sensor node PCB rev 1
2024-06-07 Update PCB with silkscreen and fix DRC violations
2024-06-07 Fix decoupling caps to be 0603 footprint
2024-06-07 Add manufacturing files for rev 1
2024-06-08 Add stm32 project template for ptn
2024-06-10 Add gitignore
    Restructure fw files
    Add adf4351 driver support
2024-06-12 Add milestone 3 sensor node FW
2024-06-12 Initial README.md commit
2024-06-23 Add heat map for M3 presentation
2024-06-23 Start PTN PCB
2024-06-24 Add loop filter
2024-06-25 Add decoupling and output matching
2024-06-25 Add 3.3V LDO, fix some EDC errors
2024-06-27 Add STM32
2024-06-27 Add RNG to payload
2024-06-27 Add a delay between sending the nRF the SPI transmission command and sending the Powercast the RESET signal
2024-06-27 Add 12V input and 5V LDO
2024-06-29 Add CAN, NRF, and PTN input terminal
2024-07-01 Add second 3V3 LDO, improve IO
2024-07-01 Add new LDO for non-PLL 3V3
2024-07-01 Add correct LED resistances
2024-07-02 Footprint assignment
2024-07-03 Complete footprint assignment
2024-07-04 Start PCB layout
2024-07-04 Organize subsystem layouts
2024-07-06 Add PCB footprints
2024-07-06 Reorganize folders
2024-07-06 Add sensor node rev 2 PCB
2024-07-06 Add basic .gitignore
2024-07-08 PTN routing
2024-07-09 PTN PCB Layout part 2
2024-07-09 Use new microcontroller package and remove some jumpers
2024-07-13 Finish routing and layout for sensor node rev 2
2024-07-13 Add to .gitignore
2024-07-14 Update STM32 footprints
2024-07-14 Finalize rev 2 for manufacturing
2024-07-14 Remove lock file
2024-07-14 Add variant of rev 2 board
2024-07-14 PTN routing part 3
2024-07-14 finish all routing for ptn
2024-07-15 complete layout pending review
2024-07-15 Add footprint and back silkscreen
2024-07-15 Add another ADP150 LDO, improve T-line
2024-07-15 Layout review and optimization
2024-07-16 Add silkscreen, add SW, fix NRF orientation, add stm32 BOOT1
2024-07-16 Add BOM and initial manufacturing files
2024-07-16 Add initial manufacturing files for sensor node rev 2s
2024-07-16 Add little guy on back silkscreen and update manufacturing files
2024-07-16 Add little guy and update manufacturing files for rev 2s
2024-07-16 Update BOM with better tolerance capacitor
2024-07-16 Fix mistake in BOM
2024-07-16 Update manufacturing files and BOM to account for different SMA connector
2024-07-16 Update silkscreen and manu files for rev 2
2024-07-16 Update silkscreen and manu files for rev 2s
2024-07-16 Update program files
2024-07-16 manufacturing ptn
2024-07-17 exclude non-purchasable items from BOM
2024-07-23 Add ENABLE_RESET macro
2024-07-23 Improve .gitignore
2024-07-23 Reorganize PCB projects and FW
2024-07-23 Update sensor node rev 2s PCB and manufacturing files
2024-07-23 Update sensor node rev 2 PCB and manufacturing files
2024-07-23 Add more SN footprints
2024-07-23 Rename sn rev folders
2024-07-23 Add sensor node rev 2 fw project
2024-07-23 Add SN datasheets
2024-07-23 Add schematic PDF for sensor node rev-2
2024-07-25 Add ptn test firmware
2024-07-25 Update sensor-node-v2 fw to work with CMake
2024-07-25 Add datasheets
2024-07-25 Add nrf2401.c/.h library code
2024-07-25 Add RNG library code
2024-07-25 Add working implementation of sensor-node-v2 firmware
2024-07-25 Update KiCad files
2024-07-25 Remove nRF config read back
2024-07-25 Remove flashing LED
2024-07-25 Add POWERCAST_RESET macro
2024-07-25 Update serial number
2024-07-29 PTN PCB STM32 Project Creation
    1. Create new cubemx project
    2. Integrate ADF4351
    3. Use timer interrupt to implement fhss
2024-07-30 Add heat map used in M3
2024-07-30 Add PTN PCB and firmware
2024-07-30 Change .gitignore
2024-07-30 Add nrf drivers to ptn, start ptn control
2024-07-30 Add .gitignore
2024-07-30 Initial project commit for ECU
2024-07-30 Update tpms archived code
2024-07-30 Update receiver code to unpack sensor message correctly
2024-07-31 Enable setting sensor node ID through Justfile and add sensor node message struct
2024-07-31 Fix struct field names
2024-07-31 Add starting CAN code
2024-07-31 Add initial code for CAN filtering
2024-07-31 Enable UART for ECU
2024-07-31 Initial commit for bluepill ECU
2024-08-01 Working CAN Rx/Tx for ECU
2024-08-01 Get basic CAN to work for PTN/ECU
2024-08-01 Modify nRF24L01+ driver to take SPI handle
2024-08-01 Update formatting and improve comments for nRF24L01+ driver
2024-08-01 Add null pointer check and comments
2024-08-01 Add CAN polling function
2024-08-01 Add NRF support
2024-08-01 Add initial implementation of full ECU fw
2024-08-02 Add CAN communication (still buggy)
2024-08-02 Fix CAN message edge case and add ptn_sn_paired as CAN signal
2024-08-02 Initial GUI commit
2024-08-03 Functional PTN firmware for 2 PTNs
2024-08-03 Organize basic grid system for GUI
2024-08-04 Add env/ folder to .gitignore
2024-08-04 Fix grid issues and make contents stretch to grid container
2024-08-04 Add tire label textboxes and current time thread
2024-08-04 Refactor code into function
2024-08-04 Implement rudimentary message parsing
2024-08-04 Add assets
2024-08-04 Add bash script to test message parsing and display
2024-08-04 Fix out-of-sync CAN message bug on ECU
2024-08-04 Add last updated time fields and threads to update them
2024-08-04 Add the status code parsing
2024-08-04 Update bash script
2024-08-06 Modify ADC pressure measurements to measure air pressure
2024-08-06 Add temperature conversion function
2024-08-07 Add urgent GUI features
2024-08-07 Add ECU firmware to keep track of ECU state and output state to GUI
2024-08-07 Add parsing for ECU state
2024-08-07 Move up static assert
2024-08-07 Remove arrows and add bindings
2024-08-07 Add PTN labels to canvas
2024-08-07 Add reset message to test scripts
2024-08-07 Add v2 of tire visual for GUI
2024-08-07 Add serial port hot-connect
2024-08-07 Update test bash script
2024-08-07 Modify serial port read delay
2024-08-08 Add ability to configure timeout of the PTN through ECU
2024-08-08 Make PTN timeout value configurable over CAN
2024-08-10 Remove ECU blue pill project
2024-08-10 Reorder labels and add reset on serial port disconnect
2024-08-10 Add hardcoded temperature reading for demo
2024-08-14 Add PCB power analysis excel file
2024-08-16 Add video and enclosure
2024-08-16 Add readme for enclosures
2024-08-16 Add readme for video
2024-08-16 Create README.md for video/
2024-08-16 Nit: update small typo in main readme
2024-08-16 Rename "enclosures" to "enclosure"
2024-08-16 Update README.md
    Rename `enclosures` to `enclosure` in README document.
